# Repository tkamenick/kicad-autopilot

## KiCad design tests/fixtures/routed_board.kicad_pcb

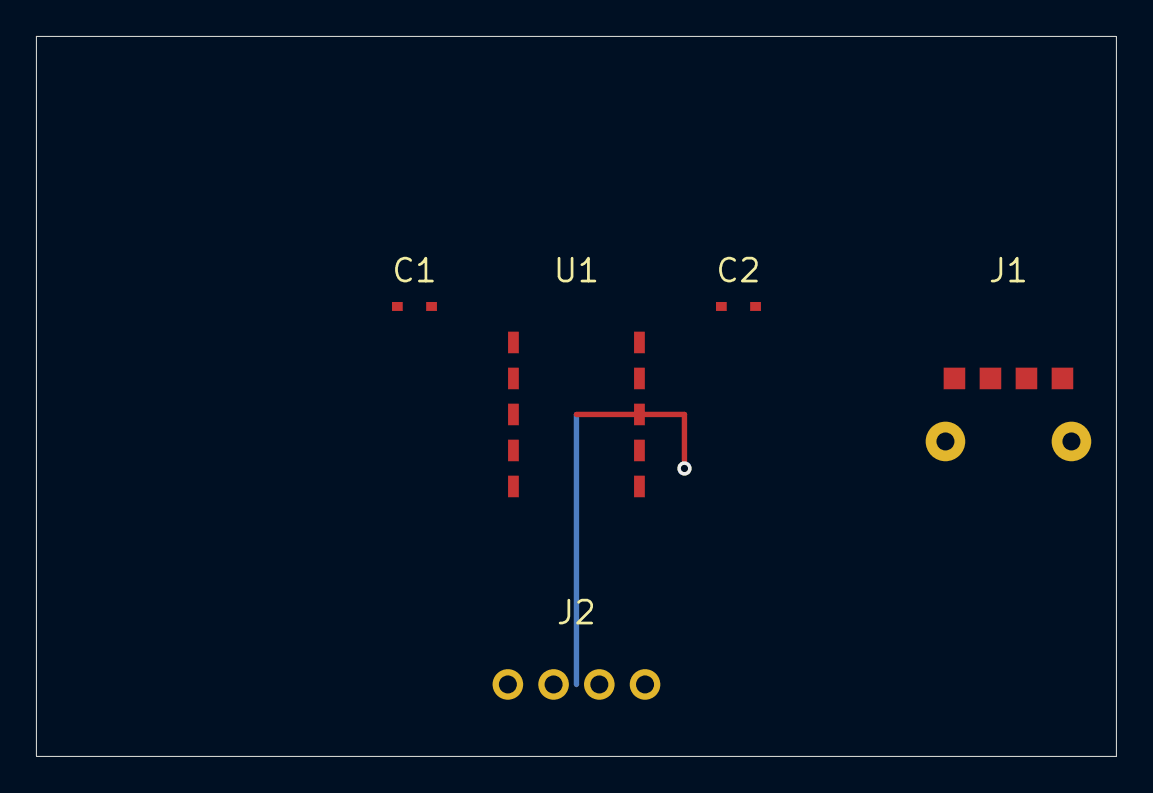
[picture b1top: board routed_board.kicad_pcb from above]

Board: 2 copper layers, 60.0 x 40.0 mm, 5 parts (0 on the bottom side), 8 nets.

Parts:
C1, C2: 100nF; C_0402
J1: RJ45
J2: DEBUG; PinHeader_1x04
U1: MCU; SOIC-10

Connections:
3V3: C1.1, C2.1, J2.2, U1.2, U1.10
GND: C1.2, C2.2, J1.5, J1.6, J2.1, U1.1, U1.9
I2C_SCL: J2.4, U1.7
I2C_SDA: J1.4, U1.6
SPI_CLK: J1.1, U1.3
SPI_CS: J1.3, U1.5
SPI_MOSI: J1.2, U1.4
UART_TX: J2.3, U1.8

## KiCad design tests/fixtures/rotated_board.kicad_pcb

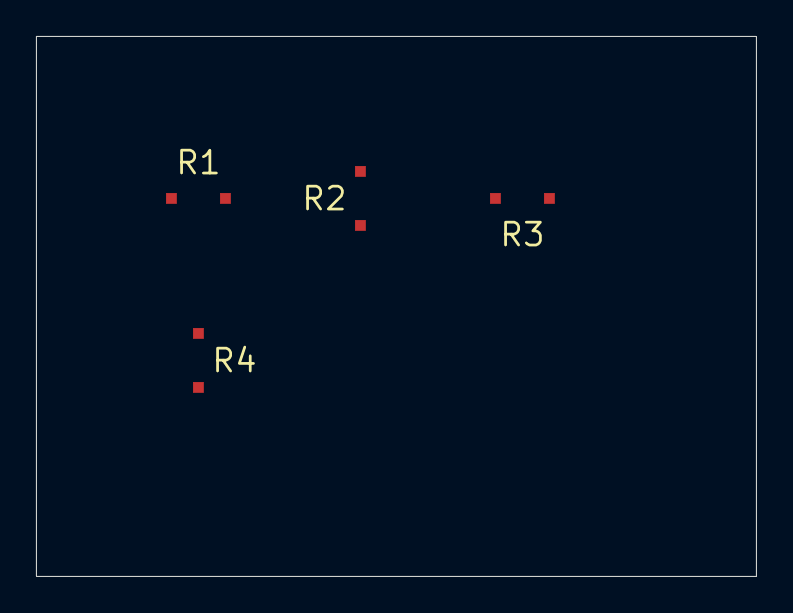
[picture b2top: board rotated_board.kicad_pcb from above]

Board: 2 copper layers, 40.0 x 30.0 mm, 4 parts (0 on the bottom side), 2 nets, no tracks yet.

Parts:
R1, R2, R3, R4: 10k; R_0402

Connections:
GND: R1.1, R2.1, R3.1, R4.1
VCC: R1.2, R2.2, R3.2, R4.2
